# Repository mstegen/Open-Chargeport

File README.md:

Open ChargePort
===============

What is it?
As the name suggests, it's a transmitter that will open the charge port of a Model S.

When I received my EU spec model S, i charged a few times with the cable Tesla supplies with the car.
The button to open the Charge port door, really is a nice feature.
As there is no such thing on a standard Type 2 charge cable, i now have to open the car door, touch the battery icon, and select open charge port. Not very convenient.

Therefore i wanted to make my own transmitter that opens the chargeport.

Credits to Banahogg who documented his attempts to analyze the RF data here
which helped me finish this project in a few days.

The components needed:

I used a 433 Mhz module connected to a PIC microcontroller. (US model S, requires a 315Mhz module)
Only a few other components are required.

1x PIC12F1822 or PIC10F200 microcontroller 
1x TX-SAW MID/3V
1x Lithium cell, 3V
2x 100nf capacitor
1x 10uf capacitor
1x pushbutton
 
Please note that the PCB layout in /eagle was designed for the PIC10F200 microcontroller.

=======================================================================================

There is now a new version, based on the same chip Tesla uses in it's Charging Cable.

The chip is a Silabs Si4010, only one external component (capacitor) is required.
I converted the Tesla specific bitstream for use with this microcontroller. 
As Silabs also provided a PCB layout file for 5 buttons, but only one button is needed, these files were modified.
The PCB layout fit's the Polycase FB-20 keyfob housing.

All files for this version can be found in the /Si4010 folder.

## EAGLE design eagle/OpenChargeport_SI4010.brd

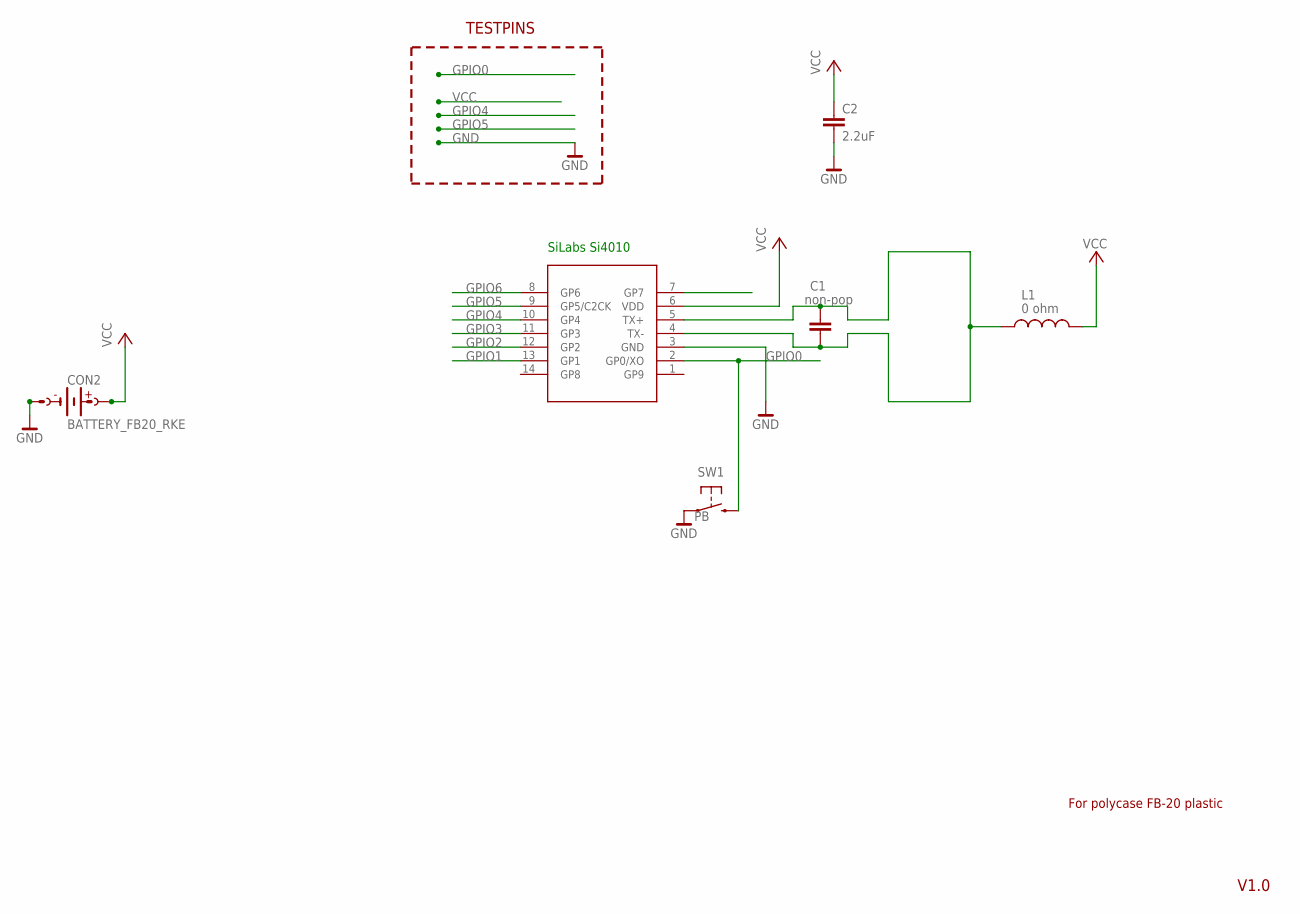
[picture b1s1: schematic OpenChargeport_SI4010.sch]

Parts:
C1: non-pop; C0603K
C2: 2.2uF; C0805K
CON2: BATTERY_FB20_RKE; BATTERY_HOLDER_CR2032F_RKE_FB20
IC1: SI4010; SOIC-14
L1: 0 ohm; L0402
SW1: PB; PUSHB_PILL

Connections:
ANT: C1.1, C1.2, IC1.4 (TX-), IC1.5 (TX+), L1.1
GND: C2.2, CON2.MINUS (NEG), CON2.MINUS1 (NEG1), IC1.3 (GND), SW1.P$1 (1)
GPIO0: IC1.2 (GP0/XO), SW1.P$2 (2)
GPIO1: IC1.13 (GP1)
GPIO2: IC1.12 (GP2)
GPIO3: IC1.11 (GP3)
GPIO4: IC1.10 (GP4)
GPIO5: IC1.9 (GP5/C2CK)
GPIO6: IC1.8 (GP6)
VCC: C2.1, CON2.PLUS1 (POS), CON2.PLUS2 (POS1), IC1.6 (VDD), L1.2

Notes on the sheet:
TESTPINS
For polycase FB-20 plastic
V1.0
SiLabs Si4010

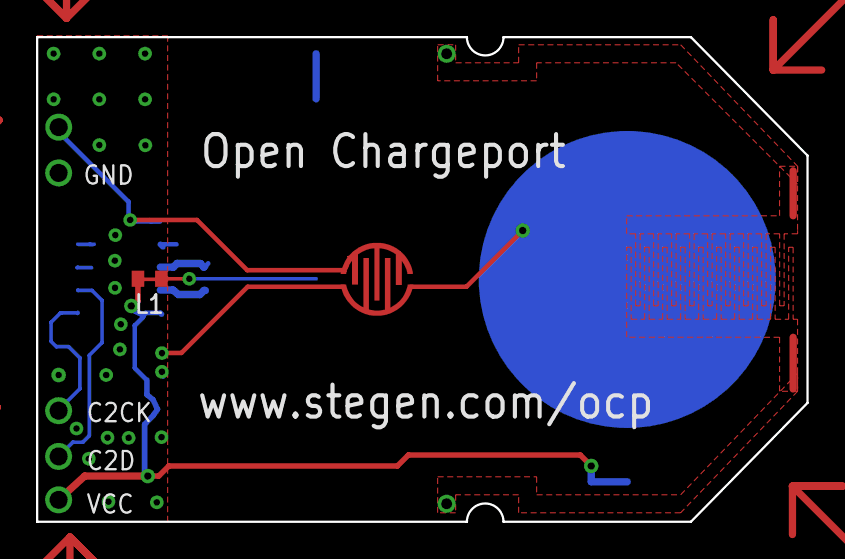
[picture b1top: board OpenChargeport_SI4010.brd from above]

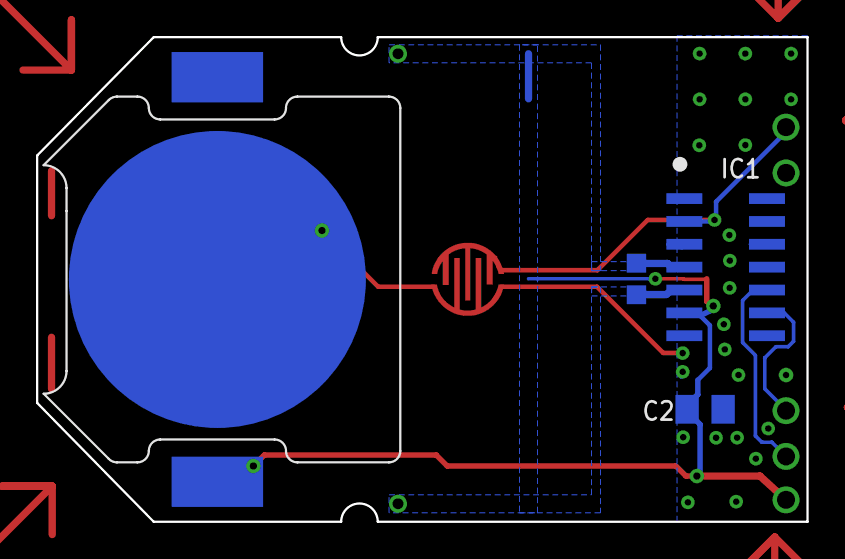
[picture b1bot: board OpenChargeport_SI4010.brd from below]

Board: 2 copper layers, 42.8 x 26.9 mm, 6 parts (4 on the bottom side), 4 nets.

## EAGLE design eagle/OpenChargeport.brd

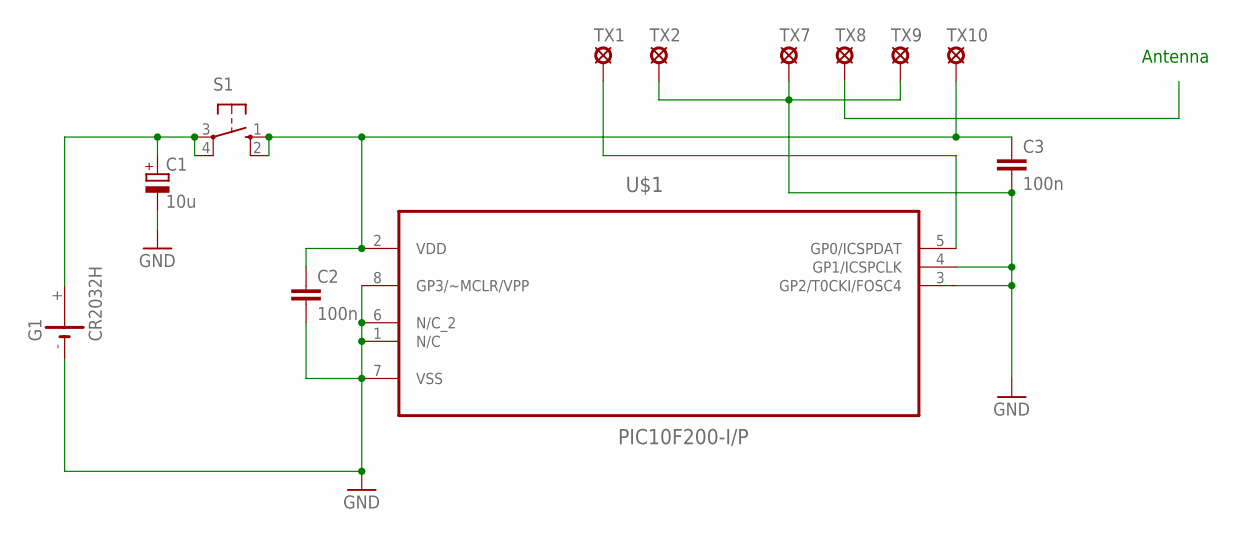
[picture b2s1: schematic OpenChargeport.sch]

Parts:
C1: 10u; E2,5-5
C2, C3: 100n; C025-025X050
G1: CR2032H
S1: 10-XX; B3F-10XX
TX1, TX2, TX7, TX8, TX9, TX10: LSP10
U$1: PIC10F200-I/P; DIP254P762X533-8

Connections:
GND: C1.-, C2.2, C3.2, G1.-, TX2.MP, TX7.MP, TX9.MP, U$1.1 (N/C), U$1.3 (GP2/T0CKI/FOSC4), U$1.4 (GP1/ICSPCLK), U$1.6 (N/C_2), U$1.7 (VSS), U$1.8 (GP3/~MCLR/VPP)
unnamed: C1.+, G1.+, S1.3, S1.4 (P1)
unnamed: C2.1, C3.1, S1.1 (S), S1.2 (S1), TX10.MP, U$1.2 (VDD)
unnamed: TX1.MP, U$1.5 (GP0/ICSPDAT)

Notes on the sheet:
Antenna

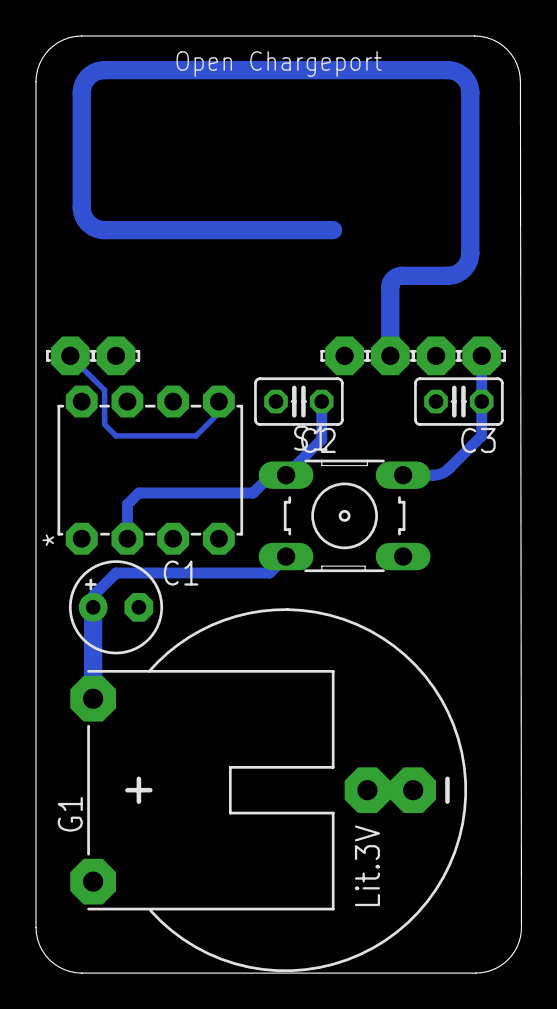
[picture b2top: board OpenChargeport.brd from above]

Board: 2 copper layers, 27.0 x 52.1 mm, 12 parts (0 on the bottom side), 4 nets.

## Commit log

2014-01-29 Added Si4010 source + PCB layout
2014-01-29 removed double files
2020-12-23 Removed purchase links
